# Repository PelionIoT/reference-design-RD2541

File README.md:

# RD2541 Introduction:

The RD2541 Reference Design is a Pelion Ready design based on Advantech WISE-1570. It is an M2.COM standardized IoT sensor node integrated with an ARM Cortex-M4 processor and NB-IoT.

The reference design is a tested and proven starting point targetted towards the creation of both Development Boards and End Products.

# Reference Design Contents:
**Reference Schematic**
This is the core of reference design, and illustrates where and how the essential components are connected.

**Example Implementation**
Based on the Reference Design, this example implementation is included to demonstrate the Reference Design being used to create real-world hardware. The example implemenation is used within Arm to include the Reference Design into the internal test infrastructure, it is comprised of two parts:

MCB (Module Carrier Board) - this has been created based on the Reference Design schematic

MTB (Module Test Bed) - this is part of the test infrastructure, and includes DAPLink circuit for programming the device, a range of I/O and loopback paths for automated testing.

**Reference Application**
Built on mbedOS, and includes Pelion Device Manager. This application has been configured to run on the Reference Design hardware, and will connect to the Pelion Cloud, and is capable of running the cloud based update service.

# Version Information:

| Release | mbed OS | mbed Cloud Client | Release Date | Comment |
| --- | --- | --- | --- | --- |
|v1.0 | 5.11.0	| 2.1.1	| 15/01/2019 | Initial Release
| |  |  |   |

Back to [Reference Designs](https://github.com/ARMmbed/reference-designs)

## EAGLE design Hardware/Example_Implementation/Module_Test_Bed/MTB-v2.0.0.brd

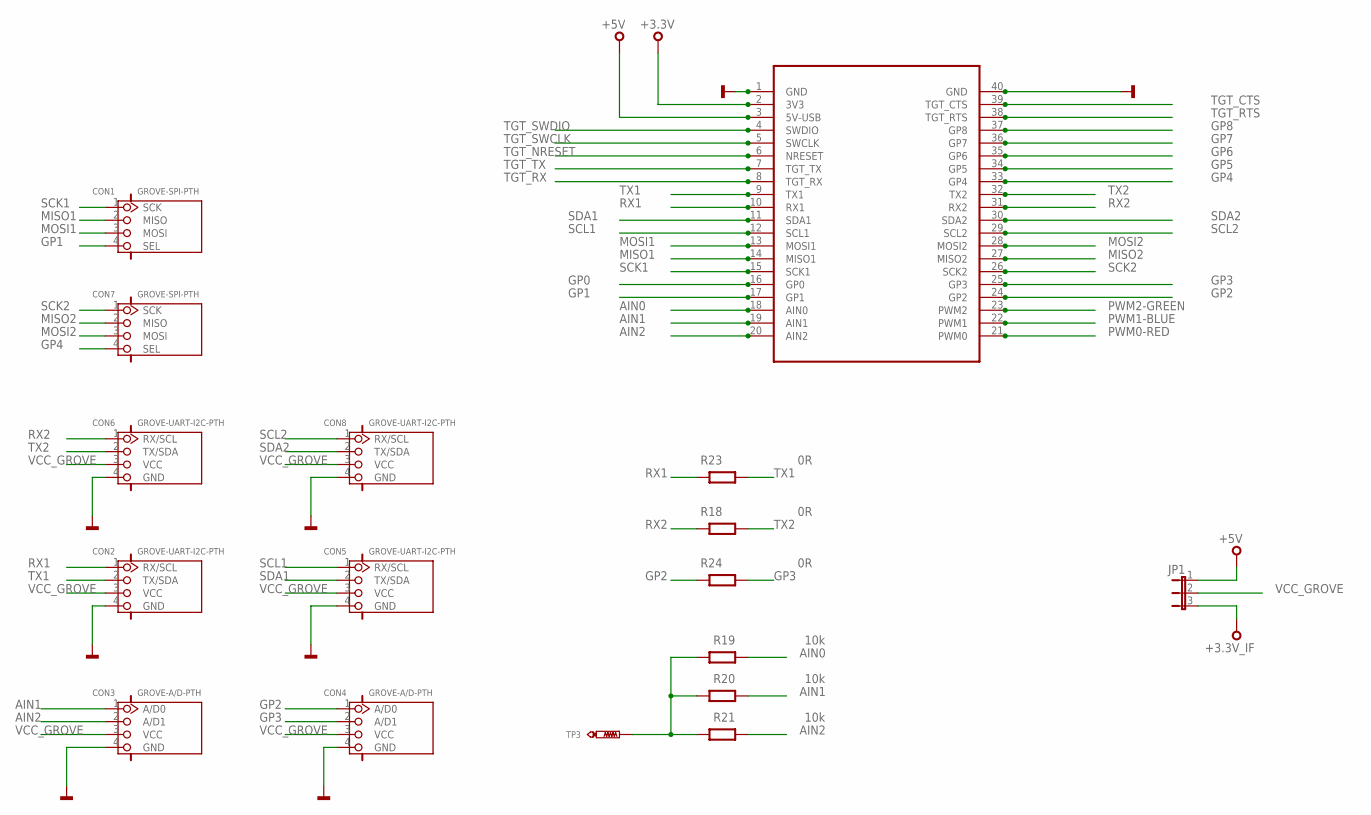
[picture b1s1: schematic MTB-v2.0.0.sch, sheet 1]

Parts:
CON1, CON7: GROVE-SPI-PTH; HW4-2.0
CON2, CON5, CON6, CON8: GROVE-UART-I2C-PTH; HW4-2.0
CON3, CON4: GROVE-A/D-PTH; HW4-2.0
JP1: JP2E; JP2
R18, R23, R24: 0R; 0603@1
R19, R20, R21: 10k; 0603@1
SKT1: MODULE_SOCKET
TP3: TEST-POINT-50R-PTH; TP50-PTH

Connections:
+3.3V: SKT1.2 (3V3), SKT1.P$42; also elsewhere on the board
+3.3V_IF: JP1.3; also elsewhere on the board
+5V: JP1.1, SKT1.3 (5V-USB), SKT1.P$43; also elsewhere on the board
AIN0: R19.1, SKT1.18 (AIN0), SKT1.P$58; also elsewhere on the board
AIN1: CON3.1 (A/D0), R20.1, SKT1.19 (AIN1), SKT1.P$59
AIN2: CON3.2 (A/D1), R21.1, SKT1.20 (AIN2), SKT1.P$60
GND: CON2.4 (GND), CON3.4 (GND), CON4.4 (GND), CON5.4 (GND), CON6.4 (GND), CON8.4 (GND), SKT1.1 (GND), SKT1.40 (GND), SKT1.P$41, SKT1.P$80; also elsewhere on the board
GP0: SKT1.16 (GP0), SKT1.P$56; also elsewhere on the board
GP1: CON1.4 (SEL), SKT1.17 (GP1), SKT1.P$57
GP2: CON4.1 (A/D0), R24.2, SKT1.24 (GP2), SKT1.P$64; also elsewhere on the board
GP3: CON4.2 (A/D1), R24.1, SKT1.25 (GP3), SKT1.P$65
GP4: CON7.4 (SEL), SKT1.33 (GP4), SKT1.P$73
GP5: SKT1.34 (GP5), SKT1.P$74; also elsewhere on the board
GP6: SKT1.35 (GP6), SKT1.P$75; also elsewhere on the board
GP7: SKT1.36 (GP7), SKT1.P$76; also elsewhere on the board
GP8: SKT1.37 (GP8), SKT1.P$77
MISO1: CON1.2 (MISO), SKT1.14 (MISO1), SKT1.P$54; also elsewhere on the board
MISO2: CON7.2 (MISO), SKT1.27 (MISO2), SKT1.P$67
MOSI1: CON1.3 (MOSI), SKT1.13 (MOSI1), SKT1.P$53; also elsewhere on the board
MOSI2: CON7.3 (MOSI), SKT1.28 (MOSI2), SKT1.P$68
unnamed: R19.2, R20.2, R21.2, TP3.TP
PWM0-RED: SKT1.21 (PWM0), SKT1.P$61; also elsewhere on the board
PWM1-BLUE: SKT1.22 (PWM1), SKT1.P$62; also elsewhere on the board
PWM2-GREEN: SKT1.23 (PWM2), SKT1.P$63; also elsewhere on the board
RX1: CON2.1 (RX/SCL), R23.2, SKT1.10 (RX1), SKT1.P$50
RX2: CON6.1 (RX/SCL), R18.2, SKT1.31 (RX2), SKT1.P$71
SCK1: CON1.1 (SCK), SKT1.15 (SCK1), SKT1.P$55; also elsewhere on the board
SCK2: CON7.1 (SCK), SKT1.26 (SCK2), SKT1.P$66
SCL1: CON5.1 (RX/SCL), SKT1.12 (SCL1), SKT1.P$52; also elsewhere on the board
SCL2: CON8.1 (RX/SCL), SKT1.29 (SCL2), SKT1.P$69; also elsewhere on the board
SDA1: CON5.2 (TX/SDA), SKT1.11 (SDA1), SKT1.P$51; also elsewhere on the board
SDA2: CON8.2 (TX/SDA), SKT1.30 (SDA2), SKT1.P$70; also elsewhere on the board
TGT_CTS: SKT1.39 (TGT_CTS), SKT1.P$79; also elsewhere on the board
TGT_NRESET: SKT1.6 (NRESET), SKT1.P$46; also elsewhere on the board
TGT_RTS: SKT1.38 (TGT_RTS), SKT1.P$78; also elsewhere on the board
TGT_RX: SKT1.8 (TGT_RX), SKT1.P$48; also elsewhere on the board
TGT_SWCLK: SKT1.5 (SWCLK), SKT1.P$45; also elsewhere on the board
TGT_SWDIO: SKT1.4 (SWDIO), SKT1.P$44; also elsewhere on the board
TGT_TX: SKT1.7 (TGT_TX), SKT1.P$47; also elsewhere on the board
TX1: CON2.2 (TX/SDA), R23.1, SKT1.9 (TX1), SKT1.P$49
TX2: CON6.2 (TX/SDA), R18.1, SKT1.32 (TX2), SKT1.P$72
VCC_GROVE: CON2.3 (VCC), CON3.3 (VCC), CON4.3 (VCC), CON5.3 (VCC), CON6.3 (VCC), CON8.3 (VCC), JP1.2

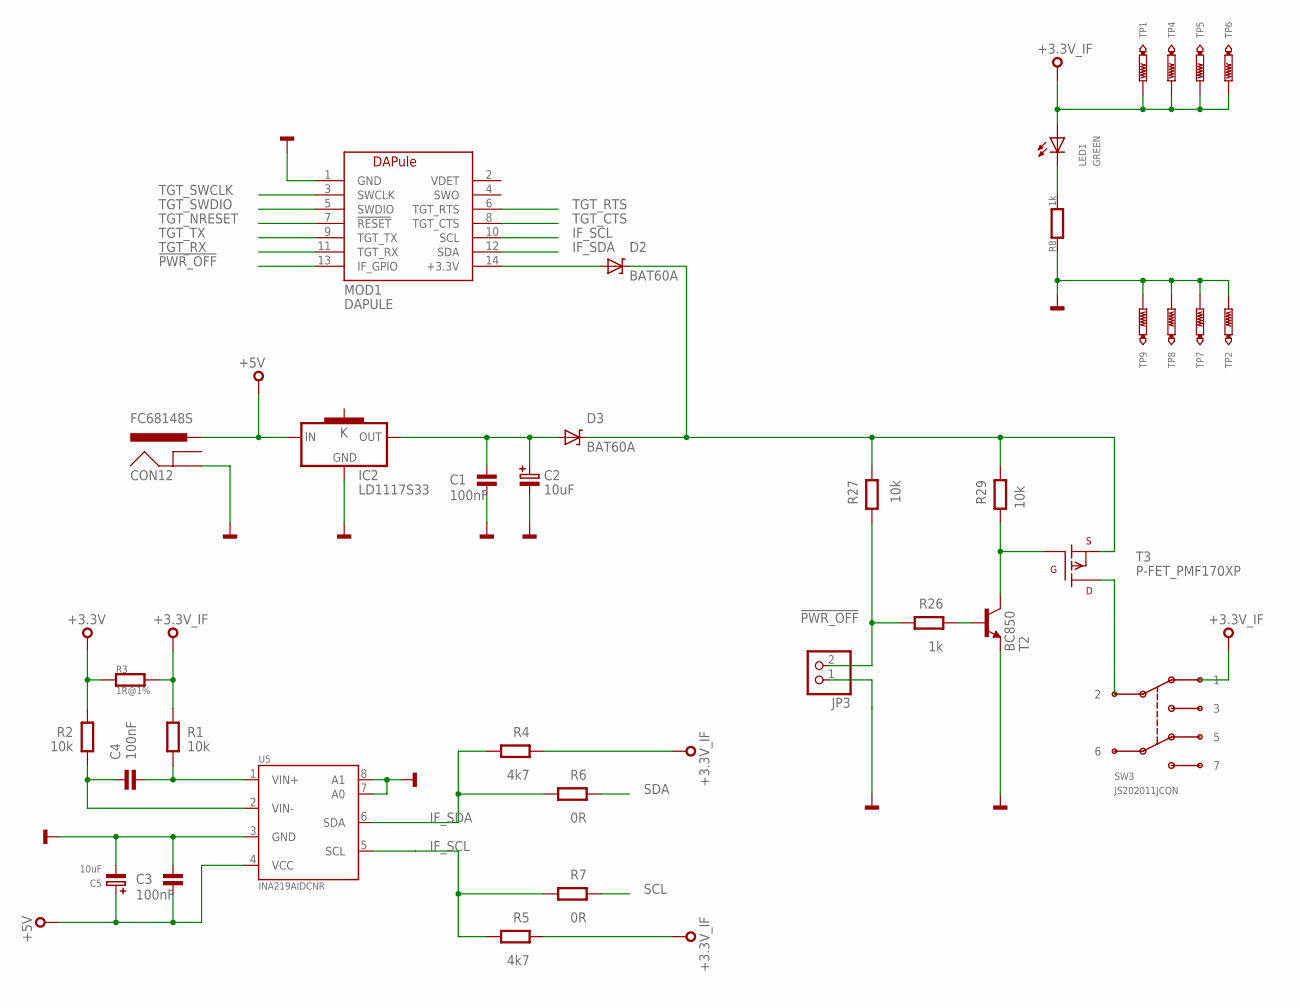
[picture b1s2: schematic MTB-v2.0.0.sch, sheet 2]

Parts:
C1, C3, C4: 100nF; 0603
C2: 10uF; SMC_B
C5: 10uF; SMC_A
CON12: FC68148S
D2, D3: BAT60A; SOD323
IC2: LD1117S33; SOT223
JP3: PINHD-1X2; 1X02
LED1: GREEN; CHIPLED_0603
MOD1: DAPULE
R1, R2, R27, R29: 10k; 0603@1
R3: 1R@1%; 0603
R4, R5: 4k7; 0603@1
R6, R7: 0R; 0603@1
R8: 1k; 0603
R26: 1k; 0603@1
SW3: JS202011JCQN
T2: BC850; SOT23
T3: P-FET_PMF170XP; SOT23-BEC
TP1, TP2, TP4, TP5, TP6, TP7, TP8, TP9: TEST-POINT-50R-PTH; TP50-PTH
U5: INA219AIDCNR; SOT23-8

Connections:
!PWR_OFF: JP3.2, MOD1.13 (IF_GPIO), R26.2, R27.2
+3.3V: R2.2, R3.1; also elsewhere on the board
+3.3V_IF: LED1.A, R1.2, R3.2, R4.1, R5.1, SW3.1, TP1.TP, TP4.TP, TP5.TP, TP6.TP; also elsewhere on the board
+5V: C3.2, C5.+, CON12.1-1 (PWR), CON12.1-2 (PWR), IC2.3 (IN), U5.4 (VCC); also elsewhere on the board
GND: C1.2, C2.-, C3.1, C5.-, CON12.3 (GND), IC2.1 (GND), JP3.1, MOD1.1 (GND), R8.1, T2.2 (E), TP2.TP, TP7.TP, TP8.TP, TP9.TP, U5.3 (GND), U5.7 (A0), U5.8 (A1); also elsewhere on the board
IF_SCL: MOD1.10 (SCL), R5.2, R7.2, U5.5 (SCL)
IF_SDA: MOD1.12 (SDA), R4.2, R6.2, U5.6 (SDA)
unnamed: C4.2, R2.1, U5.2 (VIN-)
unnamed: C4.1, R1.1, U5.1 (VIN+)
unnamed: D2.A, MOD1.14 (+3.3V)
unnamed: C1.1, C2.+, D3.A, IC2.2 (OUT)
unnamed: D2.K, D3.K, R27.1, R29.1, T3.E (S)
unnamed: R26.1, T2.1 (B)
unnamed: SW3.2, T3.C (D)
unnamed: R29.2, T2.3 (C), T3.B (G)
PA_1: LED1.C, R8.2
SCL: R7.1; also elsewhere on the board
SDA: R6.1; also elsewhere on the board
TGT_CTS: MOD1.8 (TGT_CTS); also elsewhere on the board
TGT_NRESET: MOD1.7 (!RESET); also elsewhere on the board
TGT_RTS: MOD1.6 (TGT_RTS); also elsewhere on the board
TGT_RX: MOD1.11 (TGT_RX); also elsewhere on the board
TGT_SWCLK: MOD1.3 (SWCLK); also elsewhere on the board
TGT_SWDIO: MOD1.5 (SWDIO); also elsewhere on the board
TGT_TX: MOD1.9 (TGT_TX); also elsewhere on the board

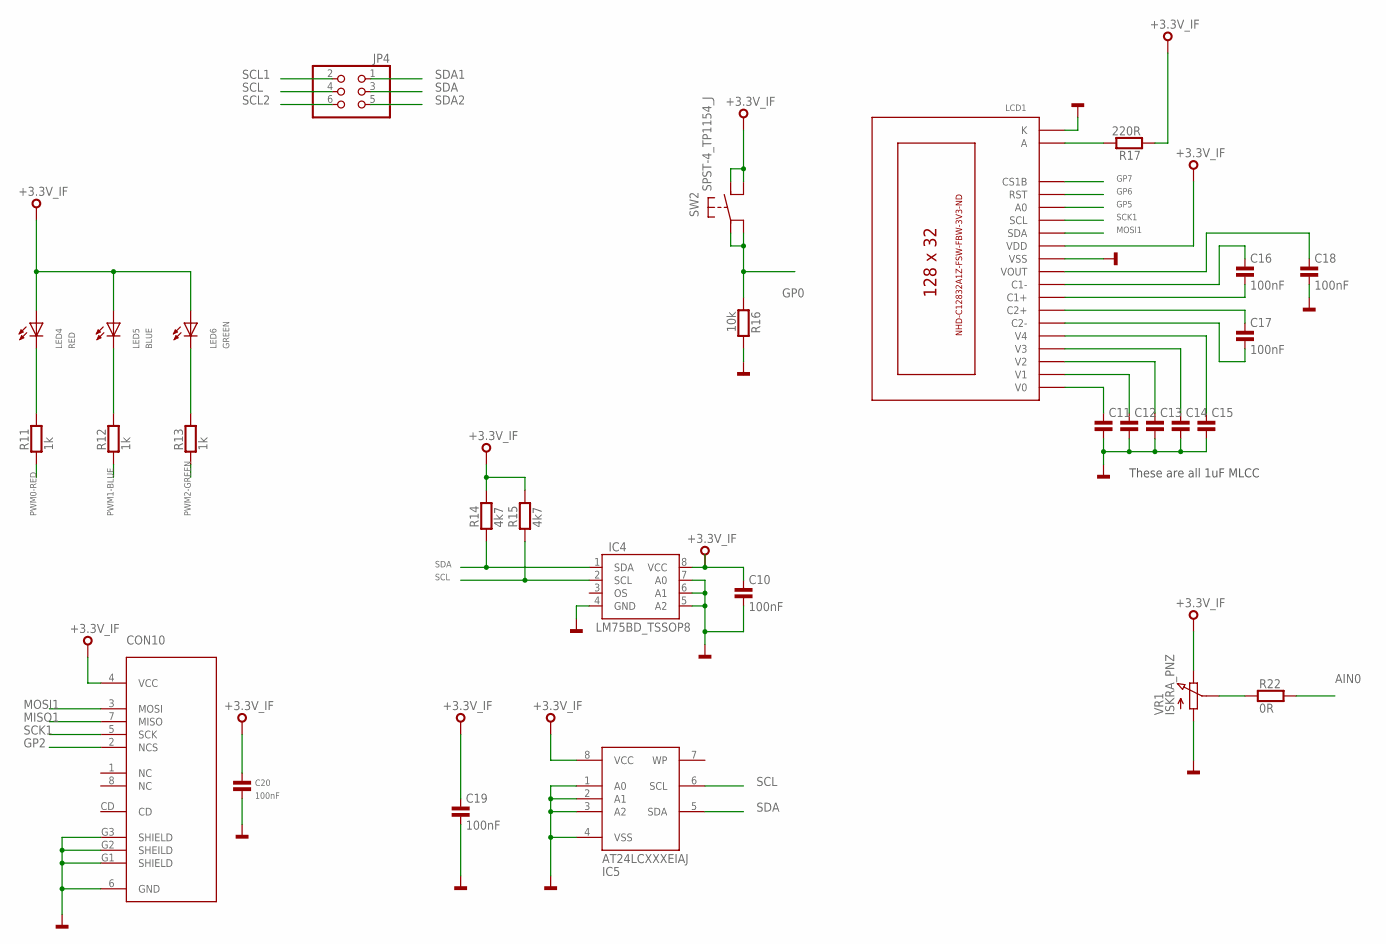
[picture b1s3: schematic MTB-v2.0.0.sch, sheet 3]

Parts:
C10, C11, C12, C13, C14, C15, C16, C17, C18, C19, C20: 100nF; 0603
CON10: MICRO-SD; AMPHENOL-101-00660-68-6
IC4: LM75BD_TSSOP8; TSSOP8
IC5: AT24LCXXXEIAJ; SO08-EIAJ
JP4: PINHD-2X3; 2X03
LCD1: C12832A1Z
LED4: RED; CHIPLED_0603
LED5: BLUE; CHIPLED_0603
LED6: GREEN; CHIPLED_0603
R11, R12, R13: 1k; 0603
R14, R15: 4k7; 0603
R16: 10k; 0603
R17: 220R; 0603
R22: 0R; 0603
SW2: SPST-4_TP1154_J; TP-1154X
VR1: ISKRA_PNZ; CA14V

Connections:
+3.3V_IF: C10.1, C19.1, C20.1, CON10.4 (VCC), IC4.8 (VCC), IC5.8 (VCC), LCD1.P$12 (VDD), LED4.A, LED5.A, LED6.A, R14.2, R15.2, R17.1, SW2.B1, SW2.B2, VR1.P$3 (E); also elsewhere on the board
AIN0: R22.2; also elsewhere on the board
GND: C10.2, C11.2, C12.2, C13.2, C14.2, C15.2, C18.2, C19.2, C20.2, CON10.6 (GND), CON10.G1 (SHIELD), CON10.G2 (SHEILD), CON10.G3 (SHIELD), IC4.4 (GND), IC4.5 (A2), IC4.6 (A1), IC4.7 (A0), IC5.1 (A0), IC5.2 (A1), IC5.3 (A2), IC5.4 (VSS), LCD1.K, LCD1.P$11 (VSS), R16.2, VR1.P$1 (A); also elsewhere on the board
GP0: R16.1, SW2.A1, SW2.A2; also elsewhere on the board
GP2: CON10.2 (NCS); also elsewhere on the board
GP5: LCD1.P$15 (A0); also elsewhere on the board
GP6: LCD1.P$16 (RST); also elsewhere on the board
GP7: LCD1.P$17 (CS1B); also elsewhere on the board
MISO1: CON10.7 (MISO); also elsewhere on the board
MOSI1: CON10.3 (MOSI), LCD1.P$13 (SDA); also elsewhere on the board
unnamed: C16.1, LCD1.P$9 (C1-)
unnamed: C17.1, LCD1.P$7 (C2+)
unnamed: C17.2, LCD1.P$6 (C2-)
unnamed: C16.2, LCD1.P$8 (C1+)
unnamed: C11.1, LCD1.P$1 (V0)
unnamed: C12.1, LCD1.P$2 (V1)
unnamed: C13.1, LCD1.P$3 (V2)
unnamed: C14.1, LCD1.P$4 (V3)
unnamed: C15.1, LCD1.P$5 (V4)
unnamed: C18.1, LCD1.P$10 (VOUT)
unnamed: LED4.C, R11.2
unnamed: LED6.C, R13.2
unnamed: LED5.C, R12.2
unnamed: LCD1.A, R17.2
unnamed: R22.1, VR1.P$2 (S)
PWM0-RED: R11.1; also elsewhere on the board
PWM1-BLUE: R12.1; also elsewhere on the board
PWM2-GREEN: R13.1; also elsewhere on the board
SCK1: CON10.5 (SCK), LCD1.P$14 (SCL); also elsewhere on the board
SCL: IC4.2 (SCL), IC5.6 (SCL), JP4.4, R15.1; also elsewhere on the board
SCL1: JP4.2; also elsewhere on the board
SCL2: JP4.6; also elsewhere on the board
SDA: IC4.1 (SDA), IC5.5 (SDA), JP4.3, R14.1; also elsewhere on the board
SDA1: JP4.1; also elsewhere on the board
SDA2: JP4.5; also elsewhere on the board

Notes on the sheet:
These are all 1uF MLCC

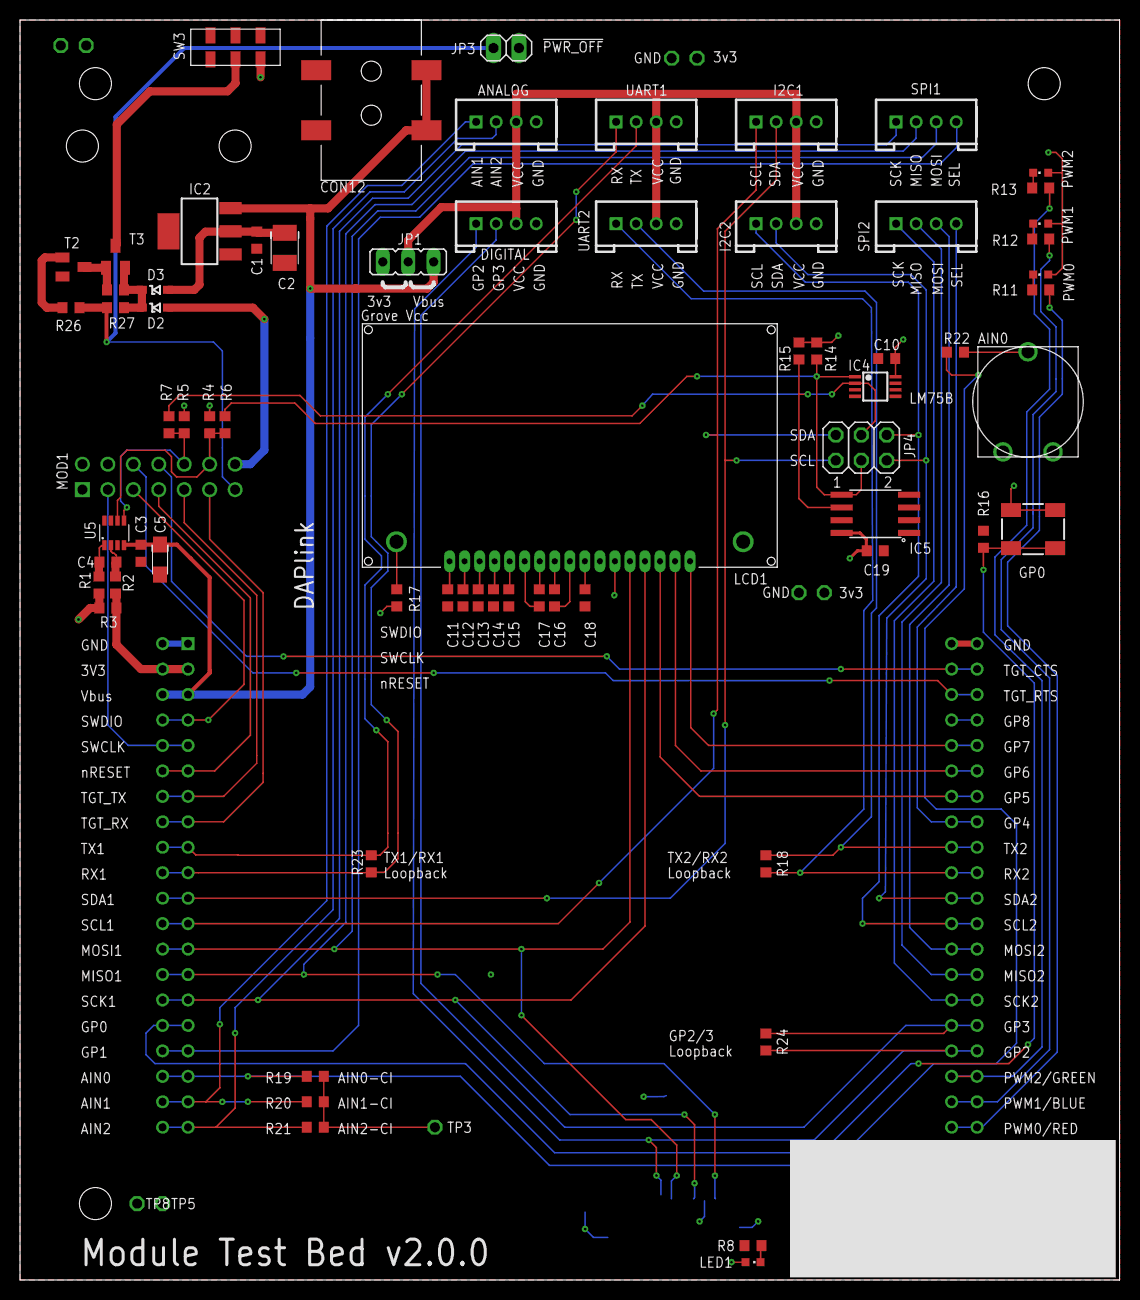
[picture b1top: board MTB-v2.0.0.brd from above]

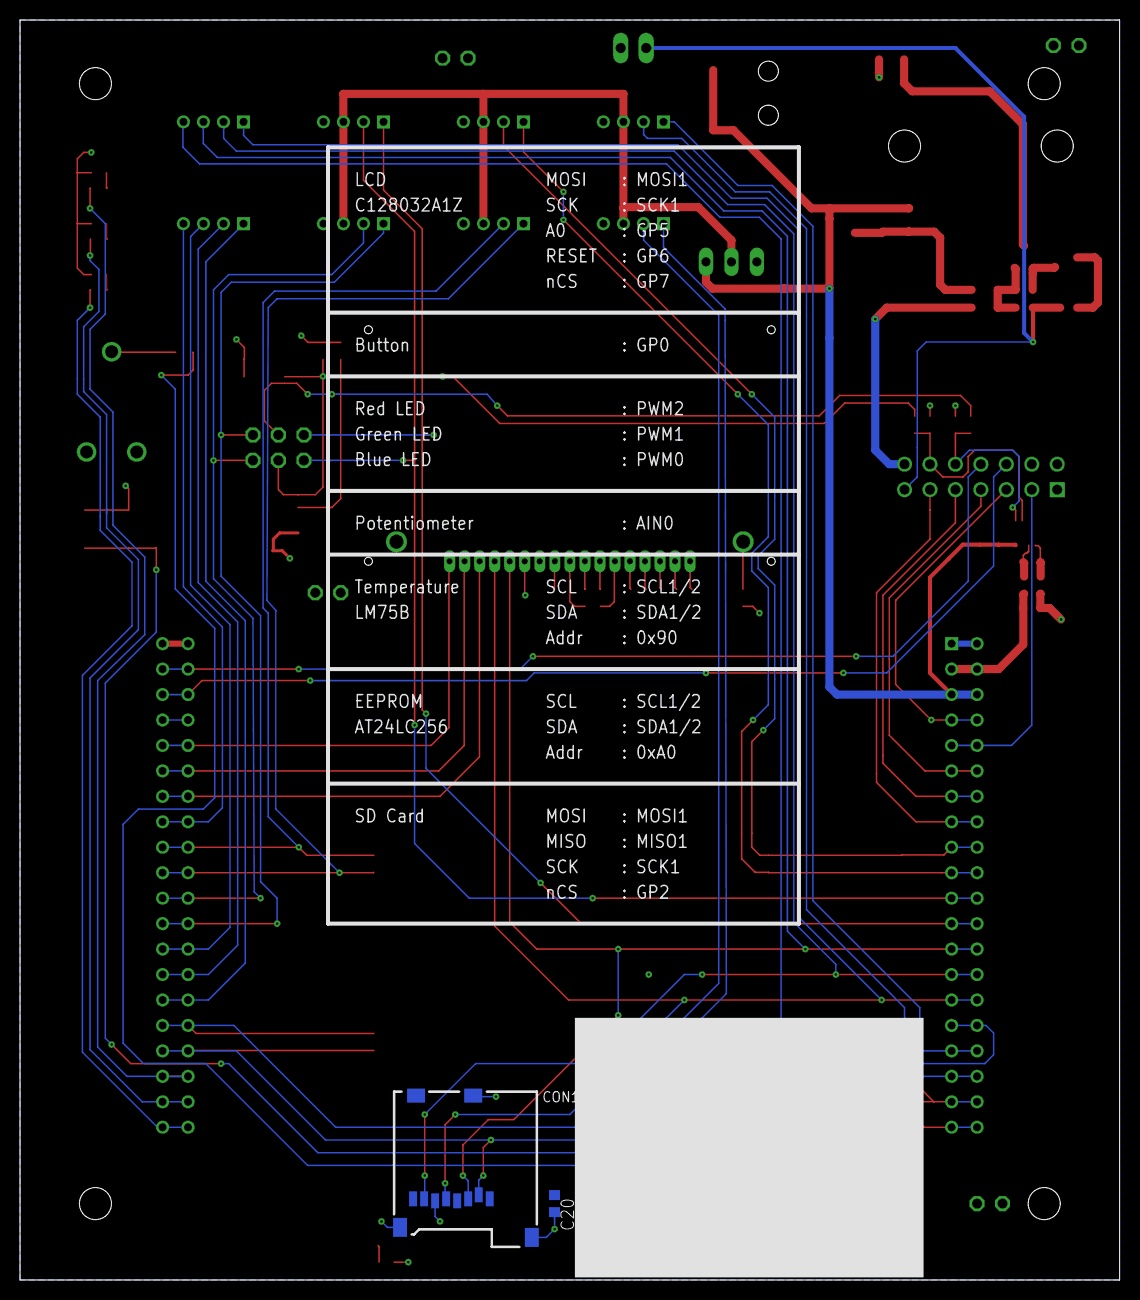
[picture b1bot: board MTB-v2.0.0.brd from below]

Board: 2 copper layers, 109.7 x 125.7 mm, 81 parts (2 on the bottom side), 71 nets.

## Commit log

2019-01-25 Reference Design RD2541 for Advantech Wise 1570
